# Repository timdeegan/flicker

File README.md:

# Lighting flicker meter

This device measures the amount and speed of flicker in light sources and screens, using a phototransistor to measure the light and a Raspberry Pi Pico for signal processing.  It was designed to be cheap (less than £10 for parts in bulk, probably more like £30 to build just one) while still accurate enough to evaluate screens and lighting for those who are sensitive to flickering light.  (For information about the effects of flickering light, see e.g. [Lehman and Wilkins, 2014](https://visualstress.info/2014-220.pdf).)

## Circuit board
The PCB is a simple 2-layer layout, easily within the cheapest tier of JLCPCB or other manufacturers.  The KiCAD files are in the [pcb](pcb/) directory, along with all the output files needed to order your own PCBs.

There are only four things to solder on:
 * Raspberry Pi Pico.  This is surface-mounted on the PCB but the connections are big enough that it's quite doable by hand. I found it helped to use some 0.1" header pins to hold one side in the right place while soldering the other side.
 * 680Ω through-hole resistor.
 * AD5220BNZ10 digital potentiometer.  This costs more than the Raspberry Pi, but is rated for the current and is a through-hole part for easy soldering.  The marking on the PCB shows which way round to mount it.
 * SFH300 phototransistor.  This must also be soldered the right way round (the flat side should match the marking on the PCB) and at the right height so it's just above the PCB when the leads are bent over.

## Case
The 3D model for the case is in [case/case.3mf](case/case.3mf).  I printed mine in PETG at 0.15mm "quality" on a Prusa i3 MK3S printer.

## Firmware
The firmware that runs on the Pico is in [firmware/flicker-v1.0.uf2](firmware/flicker-v1.0.uf2).

### Installing the firmware
First connect the board by USB while holding the BOOTSEL button, which makes it appear as a USB-attached drive.  Then copy the .uf2 file to that drive.

### Building your own firmware
The firmware source is in the [firmware](firmware) directory.  If you want to build it yourself, you will need the [Raspberry Pi Pico SDK](https://github.com/raspberrypi/pico-sdk).  Once you have the SDK installed, you should be able to build the firmware using the Visual Studio Code extension as documented in the SDK.

## How to use
The flicker meter appears as a USB serial device.
* On Windows you can use [PuTTY](https://www.chiark.greenend.org.uk/~sgtatham/putty/latest.html).  Set the connection type to "Serial", the serial line to "COM3" (or check in Device Manager to see what COM number appears when you plug in the meter) and the speed to 115200.
* On Android you can use a serial terminal app such as [Serial USB Terminal](https://play.google.com/store/apps/details?id=de.kai_morich.serial_usb_terminal&hl=en_GB&pli=1).

Point the sensor at the light you want to measure.  It's usualy best to get quite close to the light it you can, unless you see a warning about it being too bright.  The measurements appear on the serial output, along with graphs of the frequency and waveform.  The graphs work best with a monospaced font and a window at least 80 characters wide.

E.g. measuring a CFL lightbulb:

```
AGC: 66/127
--------------------------------------------------------------------------------
                  *
                 * *
                 * *
                 * *
                *  *
                *   *
                *   *
                *   *
               *    *
               *    *
               *    *
              *      *
              *      *
              *      *
              *      *  *
********     *       *  ***
*       *    *        * * *
*        ****         * * * *
                       *  ** * ***                                             *
                           * ** ************************************************
--------------------------------------------------------------------------------
FFT: peak at 100.105042Hz
FFT: peak magnitude 376468.687500
--------------------------------------------------------------------------------
          *********************                    *****************
       *******           ************           *********     **************
*********                        *********** *****                      ********
  ****                                   ******                                *

--------------------------------------------------------------------------------
Raw samples: 19ms, 10% flicker.
```

The important numbers there are `10% flicker` (the amount by which the brightness varies over one cycle of the flickering) and `100Hz` (how fast it is flickering, in this case twice the 50Hz mains electricity frequency).

By contrast, a mobile phone screen using PWM for brightness control shows a faster but much deeper flicker:
```
AGC: 127/127 (TOO DARK)
--------------------------------------------------------------------------------
                          *
                          *
                          *
                          **     *
                          **     *
                          **     *
                          **     *   *
                         * *    **   *
                         * *    **   *
                         * *    **  **
                         * *    **  ** *
                         * *    **  ** **
                         * *    **  ** **
                         * *    **  ** **
                         * *    **  ** ****
                        *  *    **  ** ****
                        *   *   **  ** ****
                        *   *   * * ** *****
         ************   *   *   * * *  *** *  ****                             *
*********            ****    ****  ***** ***************************************
--------------------------------------------------------------------------------
FFT: peak at 239.751190Hz
FFT: peak magnitude 165692.468750
--------------------------------------------------------------------------------
**************************        *******************************         ******
                      ****        ********************************        ******
                         **      **                              *       **
                          *      *                               **      *
                          *      *                                *      *
                          *      *                                *      *
                          *     **                                *     **
                          **    *                                 **    *
                           *    *                                  *    *
                           *    *                                  *    *
                           *    *                                  *    *
                           **  **                                  **  **
                            *  *                                    *  *
                            ****                                    ****
                            ****                                    ****

--------------------------------------------------------------------------------
Raw samples: 8ms, 58% flicker.
```

## Limitations
It doesn't handle very bright or very dark sources, though it will warn about them being too bright or dark.  It tends to report flicker of >60KHz when in total darkness, which I assume is noise from the Pi Pico.

The phototransistor circuit is rather simple, based on my limited knowledge at the time, and the brightness compensation is a bit clunky.  I would like to redesign it at some point with a proper variable-gain amplifier and an antialiasing filter.

I haven't tried calibrating this meter or comparing it to a properly calibrated one.  Calibrated meters are rather expensive, which is why I built this in the first place.  If you have access to proper calibration equpment and would like to test one of these meters, get in touch!

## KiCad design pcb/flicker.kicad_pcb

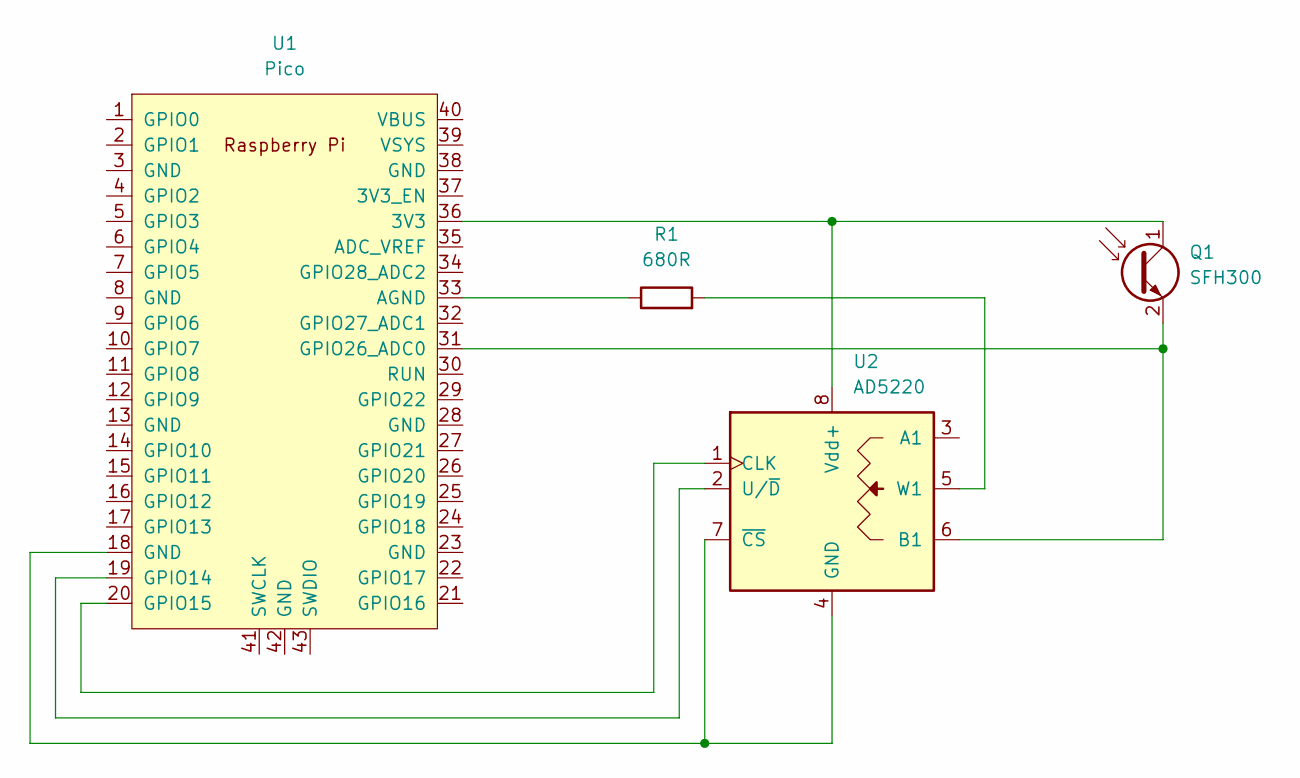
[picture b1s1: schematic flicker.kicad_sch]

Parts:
Q1: SFH300; LED_D5.0mm_Clear
R1: 680R; R_Axial_DIN0207_L6.3mm_D2.5mm_P7.62mm_Horizontal
U1: Pico; RPi_Pico_SMD_TH
U2: AD5220; DIP-8_W7.62mm

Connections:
unnamed: R1.2, U2.5 (W1)
unnamed: U1.18 (GND), U2.4 (GND), U2.7 (~CS)
unnamed: U1.19 (GPIO14), U2.2 (U/~D)
unnamed: R1.1, U1.33 (AGND)
unnamed: U1.20 (GPIO15), U2.1 (CLK)
unnamed: Q1.2 (E), U1.31 (GPIO26_ADC0), U2.6 (B1)
unnamed: Q1.1 (C), U1.36 (3V3), U2.8 (Vdd+)

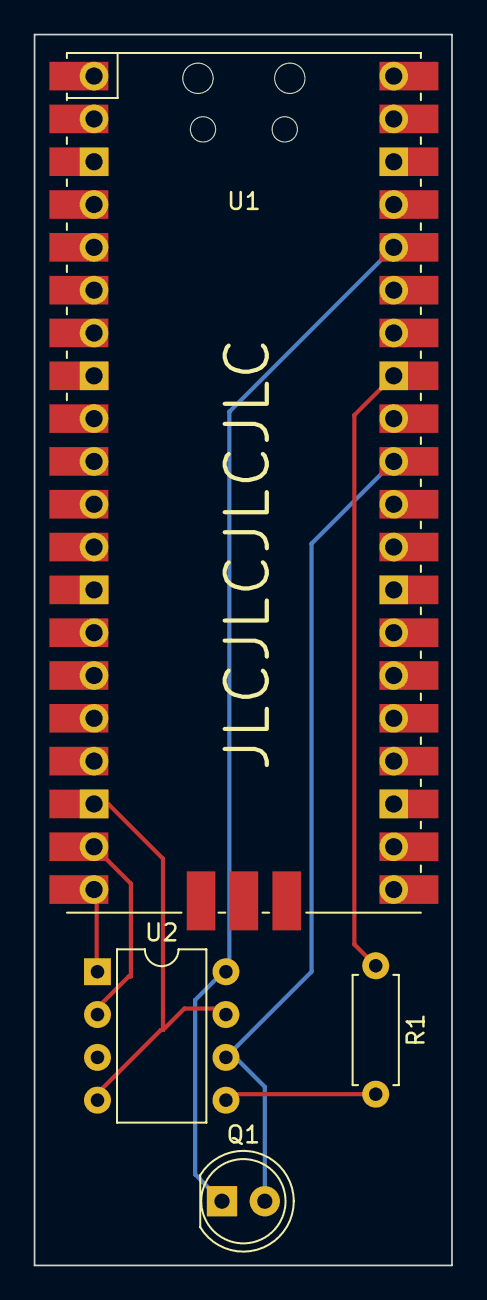
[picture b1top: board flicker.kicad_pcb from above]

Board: 2 copper layers, 24.8 x 73.0 mm, 4 parts (0 on the bottom side), 7 nets.

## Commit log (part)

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2021-03-17 Hello, world!
    Skeleton project, cmake runes, 2-clause BSD license.
2021-03-18 Turn off strict aliasing and integer overflow UB.
    We're going to reuse memory areas in ways that modern C won't
    like.
    Turn off integer overflow UB while we're at it, just to lower
    the cognitive load.
2021-04-02 Playing with FFTs in python
2021-09-12 More FFT testing
    Try a few more input waveforms, and fix existing ones.
    Start generating C tests.
2021-09-18 FFT in C
2021-09-19 Turn up the compiler warnings
2021-09-19 Unit test C FFTs
2021-09-19 Move unit tests into their own directory
2021-09-21 12-bit ADC sampling
2021-09-22 Basic graphs on the serial console.
2021-09-26 Start putting things together.
    Enough code to sample a light source, show the samples and the FFT.
    Still a fair bit missing, but it gets plausible results.
2021-09-26 Prettier graphs
2021-09-26 Detect frequency and mod%
2021-09-30 Window before FFT.
    Also move some of the DSP stuff out of main.c
2021-09-30 Interpolate to improve frequency estimate.
2021-09-30 Switch to 250kHz sampling.
    Now that we interpolate frequencies we don't care about integer
    bucket widths, so use something that divides the reference clock more
    cleanly.
2021-09-30 Avoid an edge case when sampling at 500kHz.
    The hardware doesn't seem to quite match the docs here,
    but it's easy to fix by just using 0 for 500kHz. We're
    not going anywhere near that speed but it came up in testing.
2021-10-09 PIO driver for AD5220 potentiometer.
    PIO state machine to handle up/down and clock pins, and a bit of glue
    to bring it up to where we'll need it for gain control.
2021-10-09 Test for V proportional to R.
    To check that we are really controlling the AD5220 potentiometer,
    see if the sampled levels go up and down the way they should.
    This test assumes roughly constant lighting over about 100ms,
    and that the PT current is more-or-less independent of the
    applied voltage in the operating range.
2021-10-10 Account for "wiper contact" resistance.
    The AD5220 has another 40 ohms (+/- 12) of resistance
    on the wiper terminal that needs to be included in the sums.
2022-04-30 Automatic gain control.
    Measure the peak of the waveform and adjust the potentiometer
    to bring it to a sensible level. Complain if the light is
    still too bright or too dark.
2022-04-30 Add the first 3D-printed parts.
    Enough to hold the PT with the filter in front of it.
2022-05-01 Adjusting the PT holder for a better fit.
2023-02-09 Noise improvements, part 1.
    Switch the Pico's PSU to PWM mode, which draws more power but shifts
    the noise on the 3V3 line from ~40kHz up to ~130kHz.
    Cut our own FFT off at 62kHz, to avoid noise centred around 90kHz that
    I wasn't able to fix by throwing capacitors at it. That's half the
    Nyquist frequency, which is probably still optimistic.
2023-02-11 Swap clock and up/down pins on the AD5220
2023-02-11 First attempt at PCB layout
2023-02-13 Move firmware into its own directory
2023-02-13 UI: default Android app
2023-02-13 Don't track Android IDE config in git
2023-02-17 UI: auto-start based on USB ID
    Filter on the Pico's UART device for now. I should change that
    to a proper VID/PID later so the app doesn't have to wake for
    every Pico ever. The Pi docs suggest filtering on the USB
    *strings* but the Android SDK only filters on ID numbers. :(
2023-02-26 Firmware: slower AD5220 clock
2026-05-29 Remove partial UI app and SCAD files
    These were never complete enough to be useful.
2026-05-29 PCB: use complete part number for AD5220BNZ10
2026-05-29 Add a README
2026-05-30 Add the case
